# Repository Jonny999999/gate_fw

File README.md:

Custom pcb-design and firmware for an esp32 controlling a self-made automated sliding gate.  
Full Documentation: https://pfusch.zone/automated-sliding-gate

# Changelog V2.0
- Replace old multipurpose board with a custom pcb for controlling the gate
- custom pcb:
  - fully isolate microcontroller from long cables and VFD noise
  - RS485 interface
  - Servo interface to lock the gate
  - Preparation for Encoders
- control motors with VFDs instead of Relays
- firmware rework or rewrite

<br>

## pcb v2.0-isolated-gate-control
- **[KiCad Project](pcb_v2.0-isolated-gate-control/)**
- **[Schematic.pdf](pcb_v2.0-isolated-gate-control/export/schematic.pdf)**
- **[G-code for Isolation Milling](pcb_v2.0-isolated-gate-control/pcb2gcode)**  
  
- **[Connection plan](doc/V2.0_connection-plan.drawio.pdf)**

Schematic + layout preview:  
<p align="center">

</p>

<br>

## Photos
Photos of the V2.0 hardware setup (new custom made pcb, control cabinet and additional box with outsourced power supply and VFDs)

<br>

# Installation
### Install esp-idf
For this project **ESP-IDF v5.5.1** is required  
(with other versions it most likely will not compile)
```bash
#clone the esp-idf repository and check out the required version
git clone -b v5.5.1 --recursive https://github.com/espressif/esp-idf.git ~/esp/v5.5.1/esp-idf
#run installation script in the cloned folder
~/esp/v5.5.1/esp-idf/install.sh esp32
```
### Clone this repo
```
git clone git@github.com:Jonny999999/gate_fw.git
```

# Compilation
### Set up environment
```bash
source ~/esp/v5.5.1/esp-idf/export.sh
```
(run once per terminal)

### Compile
```bash
idf.py build
```

### Upload
**Important:** Since V2.0 the **east Gate has to be slightly open for the upload to work**  
(Since the gpio used for limit switch fully closed has to be pulled low during flashing)
- connect micro-usb cable to ESP32 module on pcb
- press REST and BOOT button
- release RESET button (keep pressing boot)
- run flash command:
```bash
idf.py flash
```
- once "connecting...' successfully, BOOT button can be released  

# Usage

## Quick guide — print this and put it next to the button

### Open button

| What you do | What the gate does |
|---|---|
| **Press briefly** | opens a small gap, enough to walk through |
| **Press briefly again**, right away | makes the gap wider — once for every extra press |
| **Hold** until you hear a long beep | opens fully and stays open |
| **Keep holding** until two short beeps follow | opens fully, then closes again by itself |
| **Press briefly, then press and hold** | opens a small gap, then closes again by itself |

The gate starts moving the moment you press. Just let go when you hear what you want.

### Close button
Press once — the gate closes.

### Remote control
**A** opens fully · **B** closes.

### Stop / cancel
Press **any** button while the gate is moving, or while it is waiting to close by itself.

### When the gate closes by itself
It waits until nobody has crossed the light barrier for a while —
about **10 seconds** after a small gap, about **2 minutes** after opening fully.
Walking through again restarts the wait, so take your time.
The beeps get faster just before it starts moving.
The red lamp flashes briefly once a second for as long as a self-close is waiting.

<br>

---

## Details

### The open button, held down
The gate starts opening the moment you press, and holding on escalates. **Release when you
hear what you want** - each stage announces itself:

| Hold | Meaning | You hear |
|---|---|---|
| release quickly | small gap | one short beep |
| ~0.8 s | open completely | one long tone |
| ~2.5 s | open completely **and close again afterwards** | long tone, then two short ones |

Nothing is committed until you let go, so the familiar "hold it down to open the gate fully"
gesture is unchanged - you simply now have the option of holding on a moment longer.

### Close behind me
Two ways in, depending on how wide you need it:

- **Short press, then press and hold** - opens the small gap, for walking through.
- **Hold the first press ~2.5 s** - opens completely, for driving out.

Either way the gate closes again on its own **once the light barrier has been continuously
free for long enough** - not simply a fixed time after opening.

That distinction is the point: the gate waits until everybody is actually through and
nothing else is coming. Walking in and out, or taking a while with a trailer, restarts the
wait instead of racing a deadline.

| Opening | Barrier must stay clear for |
|---|---|
| small gap (walking through) | 10 s |
| fully open (driving out) | 120 s |

The full opening waits much longer on purpose: you open the gate, walk to the car, start it
and drive out - the barrier may not be interrupted at all for a minute or more, and the gate
must not close in front of you meanwhile.

- An accelerating beep countdown announces the closing over the last 4 seconds, the same one
  the gate uses whenever it starts moving by itself. Interrupting the light barrier during
  the countdown restarts the wait - audibly, because the beeping stops.
- If the light barrier stays interrupted for 20 seconds without a break, the gate gives up
  and stays open (two short beeps, then a long one). Whoever is there is clearly busy.
- Pressing **open** cancels it and leaves the gate open. Pressing **close** closes
  immediately instead of waiting.
- If the barrier is interrupted while it is already closing, it behaves like any other
  close: it pauses, and resumes 4 seconds after the way is clear again.

### Red LED
Two shapes, told apart at a glance:

- **Even blinking** - something went wrong. The faster, the more serious. The LED keeps
  showing the last problem until the next movement is started.
- **Short flash with a gap** - nothing is wrong, but the gate will move on its own in a
  while. Any button press calls it off.

| Pattern | Meaning |
|---|---|
| even, very fast (10/s) | VFD communication failed - the drives could not be reached |
| even, fast (2.5/s) | movement timeout - a limit switch was not reached in time |
| even, slow (1/s) | motor current too high - something was in the way while closing |
| even, very slow (0.5/s) | the light barrier stayed blocked, the movement was given up |
| flash every 0.5 s | movement paused, waiting for the light barrier to clear |
| flash every second | an automatic close is pending |
| steady on (while idle) | the light barrier is interrupted (useful for aligning it) |

The green panel LED is wired in parallel with the buzzer and simply echoes the beeps.

<br>

---

# Legacy -  Old Version V1.0
Left: Photo of control-pcb + RC-module (V1.0)  
Right: Photo of cabinet with power relays and V0.1 board (in V1.0 new board version was used and outsourced due to EMV issues when switching)

# Schema

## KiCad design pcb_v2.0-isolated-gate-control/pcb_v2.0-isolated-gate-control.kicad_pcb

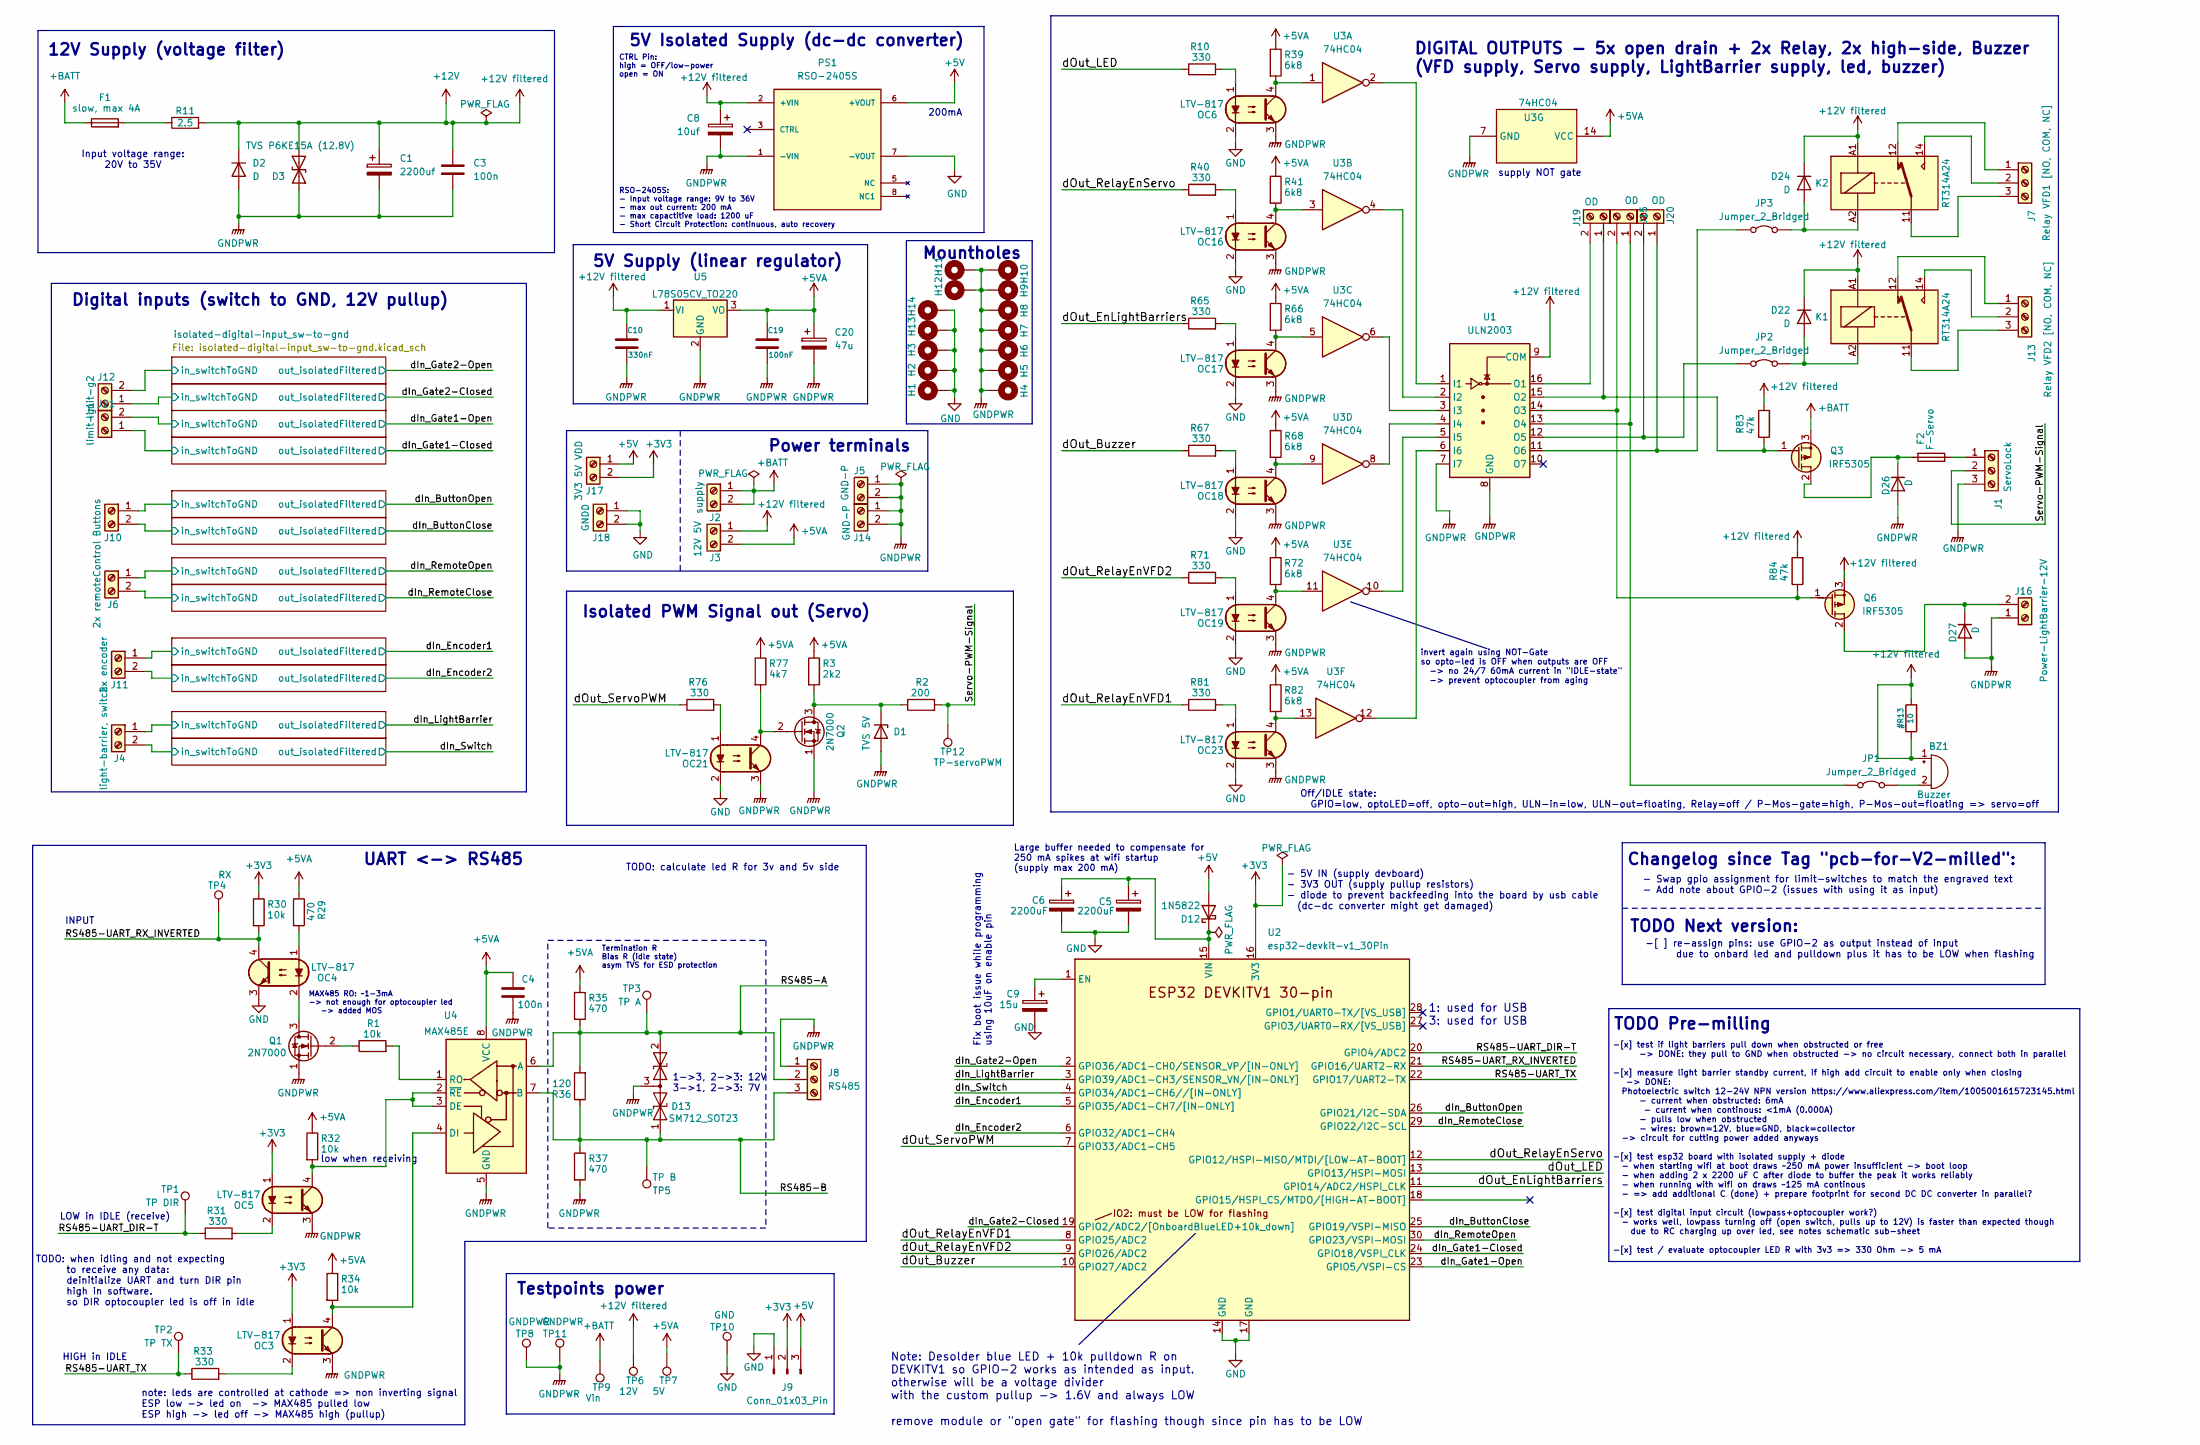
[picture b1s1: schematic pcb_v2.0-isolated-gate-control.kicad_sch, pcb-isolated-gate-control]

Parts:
BZ1: Buzzer; Buzzer_TDK_PS1240P02BT_D12.2mm_H6.5mm
C1: 2200uf; CP_Radial_D10.0mm_P3.80mm
C3, C4: 100n; C_Disc_D7.0mm_W2.5mm_P5.00mm
C5, C6: 2200uF; CP_Radial_D10.0mm_P5.00mm
C8: 10uf; CP_Radial_D5.0mm_P2.50mm
C9: 15u; CP_Radial_D6.3mm_P2.50mm
C10: 330nF; C_Disc_D8.0mm_W5.0mm_P5.00mm
C19: 100nF; C_Disc_D7.0mm_W2.5mm_P5.00mm
C20: 47u; CP_Radial_D5.0mm_P2.50mm
D1: TVS 5V; D_5W_P5.08mm_Vertical_AnodeUp
D2, D22, D24: D; D_T-1_P12.70mm_Horizontal
D3: TVS P6KE15A (12.8V); D_DO-201AE_P15.24mm_Horizontal
D12: 1N5822; D_DO-201AD_P15.24mm_Horizontal
D13: SM712_SOT23; SOT-23
D26, D27: D; D_DO-201_P5.08mm_Vertical_KathodeUp
F1: slow, max 4A; Fuseholder_Automotive-Mini_Fuse11x4x16_Footprint15x5_Inline
F2: F-Servo; Fuseholder_Automotive-Mini_Fuse11x4x16_Footprint15x5_Inline
H1, H2, H3, H4, H5, H6, H7, H8, H9, H10, H11, H12, H13, H14: MountingHole_Pad; MountingHole_2.2mm_NPTH-with-pad_DRC-clearance-error
J1: ServoLock; ScrewTerminal_P5mm_3Pin_FP15x8
J2: supply; ScrewTerminal_P5mm_2Pin_FP10x8
J3: 12V 5V; ScrewTerminal_P5mm_2Pin_FP10x8
J4: light-barrier, switch; ScrewTerminal_P5mm_2Pin_FP10x8
J5, J14: GND-P; ScrewTerminal_P5mm_2Pin_FP10x8
J6: 2x remoteControl; ScrewTerminal_P5mm_2Pin_FP10x8
J7: Relay VFD1 [NO, COM, NC]; ScrewTerminal_P5mm_3Pin_FP15x8
J8: RS485; ScrewTerminal_P5mm_3Pin_FP15x8
J9: Conn_01x03_Pin; PinHeader_1x03_P2.54mm_Vertical
J10: Buttons; ScrewTerminal_P5mm_2Pin_FP10x8
J11: 2x encoder; ScrewTerminal_P5mm_2Pin_FP10x8
J12: limit-g2; ScrewTerminal_P5mm_2Pin_FP10x8
J13: Relay VFD2 [NO, COM, NC]; ScrewTerminal_P5mm_3Pin_FP15x8
J15, J19, J20: OD; ScrewTerminal_P5mm_2Pin_FP10x8
J16: Power-LightBarrier-12V; ScrewTerminal_P5mm_2Pin_FP10x8
J17: 3V3 5V VDD; ScrewTerminal_P5mm_2Pin_FP10x8
J18: GNDD; ScrewTerminal_P5mm_2Pin_FP10x8
J21: limit-g1; ScrewTerminal_P5mm_2Pin_FP10x8
JP1, JP2, JP3: Jumper_2_Bridged; Jumper_P2.54mm_D0.7mm
K1, K2: RT314A24; Relay_SPDT_Schrack-RT1-16A-FormC_RM5mm
OC3, OC4, OC5, OC6, OC16, OC17, OC18, OC19, OC21, OC23: LTV-817; DIP-4_W10.16mm_LongPads
PS1: RSO-2405S; CONV_RSO-2405S; PARTREV 3
Q1, Q2: 2N7000; TO-92_HandSolder
Q3, Q6: IRF5305; TO-220-3_Vertical
R1, R30, R32, R34: 10k; R_Axial_DIN0207_L6.3mm_D2.5mm_P2.54mm_Vertical
R2: 200; R_Axial_DIN0207_L6.3mm_D2.5mm_P2.54mm_Vertical
R3: 2k2; R_Axial_DIN0207_L6.3mm_D2.5mm_P2.54mm_Vertical
R10, R31, R33, R40, R65, R67, R71, R76, R81: 330; R_Axial_DIN0207_L6.3mm_D2.5mm_P2.54mm_Vertical
R11: 2.5; Cement-Power-R_L22_W10_P23_Horizontal
R29, R35, R37: 470; R_Axial_DIN0207_L6.3mm_D2.5mm_P10.16mm_Horizontal
R36: 120; R_Axial_DIN0207_L6.3mm_D2.5mm_P2.54mm_Vertical
R39, R41, R66, R68, R72, R82: 6k8; R_Axial_DIN0207_L6.3mm_D2.5mm_P2.54mm_Vertical
R77: 4k7; R_Axial_DIN0207_L6.3mm_D2.5mm_P10.16mm_Horizontal
R83: 47k; R_Axial_DIN0207_L6.3mm_D2.5mm_P10.16mm_Horizontal
R84: 47k; R_Axial_DIN0207_L6.3mm_D2.5mm_P2.54mm_Vertical
TP1: TP DIR; PinHeader_1x01_P2.54mm_Vertical
TP2: TP TX; PinHeader_1x01_P2.54mm_Vertical
TP3: TP A; PinHeader_1x01_P2.54mm_Vertical
TP4: RX; PinHeader_1x01_P2.54mm_Vertical
TP5: TP B; PinHeader_1x01_P2.54mm_Vertical
TP6: 12V; PinHeader_1x01_P2.54mm_Vertical
TP7: 5V; PinHeader_1x01_P2.54mm_Vertical
TP8, TP11: GNDPWR; PinHeader_1x01_P2.54mm_Vertical
TP9: Vin; PinHeader_1x01_P2.54mm_Vertical
TP10: GND; PinHeader_1x01_P2.54mm_Vertical
TP12: TP-servoPWM; PinHeader_1x01_P2.54mm_Vertical
U1: ULN2003; DIP-16_W7.62mm_LongPads
U2: esp32-devkit-v1_30Pin
U3: 74HC04; DIP-14_W7.62mm_LongPads
U4: MAX485E; DIP-8_W7.62mm_LongPads
U5: L78S05CV_TO220; TO-220-3_Vertical

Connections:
+3V3: J9.2, J17.2, OC3.1, OC5.1, R30.1, U2.16 (3V3); also elsewhere on the board
+5V: D12.2 (A), J9.3, J17.1, PS1.6 (+VOUT)
+5VA: C4.1, C19.1, C20.1, J3.2, R3.1, R29.1, R32.1, R34.1, R35.1, R39.1, R41.1, R66.1, R68.1, R72.1, R77.1, R82.1, TP7.1, U3.14 (VCC), U4.8 (VCC), U5.3 (VO)
+12V: BZ1.1 (+), C1.1, C3.1, C8.1, C10.1, D2.1 (K), D3.1 (A1), D22.1 (K), D24.1 (K), J3.1, K1.A1, K2.A1, PS1.2 (+VIN), Q6.3 (S), R11.2, R83.2, R84.2, TP6.1, U1.9 (COM), U5.1 (VI); also elsewhere on the board
+BATT: F1.1, J2.1, J2.2, Q3.3 (S), TP9.1
/RS485-A: D13.2 (A2), J8.2, R35.2, R36.2, TP3.1, U4.6 (A)
/RS485-B: D13.1 (A1), J8.3, R36.1, R37.1, TP5.1, U4.7 (B)
/RS485-UART_DIR-T: R31.1, TP1.1, U2.20 (GPIO4/ADC2)
/RS485-UART_RX_INVERTED: OC4.4, R30.2, TP4.1, U2.21 (GPIO16/UART2-RX)
/RS485-UART_TX: R33.1, TP2.1, U2.22 (GPIO17/UART2-TX)
/Servo-PWM-Signal: J1.2, R2.2, TP12.1
/dIn_ButtonClose: U2.25 (GPIO19/VSPI-MISO); also elsewhere on the board
/dIn_ButtonOpen: U2.26 (GPIO21/I2C-SDA); also elsewhere on the board
/dIn_Encoder1: U2.5 (GPIO35/ADC1-CH7/[IN-ONLY]); also elsewhere on the board
/dIn_Encoder2: U2.6 (GPIO32/ADC1-CH4); also elsewhere on the board
/dIn_Gate1-Closed: U2.24 (GPIO18/VSPI_CLK); also elsewhere on the board
/dIn_Gate1-Open: U2.23 (GPIO5/VSPI-CS); also elsewhere on the board
/dIn_Gate2-Closed: U2.19 (GPIO2/ADC2); also elsewhere on the board
/dIn_Gate2-Open: U2.2 (GPIO36/ADC1-CH0/SENSOR_VP/[IN-ONLY]); also elsewhere on the board
/dIn_LightBarrier: U2.3 (GPIO39/ADC1-CH3/SENSOR_VN/[IN-ONLY]); also elsewhere on the board
/dIn_RemoteClose: U2.29 (GPIO22/I2C-SCL); also elsewhere on the board
/dIn_RemoteOpen: U2.30 (GPIO23/VSPI-MOSI); also elsewhere on the board
/dIn_Switch: U2.4 (GPIO34/ADC1-CH6//[IN-ONLY]); also elsewhere on the board
/dOut_Buzzer: R67.1, U2.10 (GPIO27/ADC2)
/dOut_EnLightBarriers: R65.1, U2.11 (GPIO14/ADC2/HSPI_CLK)
/dOut_LED: R10.1, U2.13 (GPIO13/HSPI-MOSI)
/dOut_RelayEnServo: R40.1, U2.12 (GPIO12/HSPI-MISO/MTDI/[LOW-AT-BOOT])
/dOut_RelayEnVFD1: R81.1, U2.8 (GPIO25/ADC2)
/dOut_RelayEnVFD2: R71.1, U2.9 (GPIO26/ADC2)
/dOut_ServoPWM: R76.1, U2.7 (GPIO33/ADC1-CH5)
/isolated-digital-input_sw-to-gnd1/in_switchToGND: J12.1; also elsewhere on the board
/isolated-digital-input_sw-to-gnd2/in_switchToGND: J21.2; also elsewhere on the board
/isolated-digital-input_sw-to-gnd3/in_switchToGND: J21.1; also elsewhere on the board
/isolated-digital-input_sw-to-gnd4/in_switchToGND: J10.1; also elsewhere on the board
/isolated-digital-input_sw-to-gnd5/in_switchToGND: J10.2; also elsewhere on the board
/isolated-digital-input_sw-to-gnd6/in_switchToGND: J11.1; also elsewhere on the board
/isolated-digital-input_sw-to-gnd7/in_switchToGND: J11.2; also elsewhere on the board
/isolated-digital-input_sw-to-gnd8/in_switchToGND: J6.1; also elsewhere on the board
/isolated-digital-input_sw-to-gnd9/in_switchToGND: J6.2; also elsewhere on the board
/isolated-digital-input_sw-to-gnd10/in_switchToGND: J4.1; also elsewhere on the board
/isolated-digital-input_sw-to-gnd/in_switchToGND: J12.2; also elsewhere on the board
GND: C5.2, C6.2, C9.2, H1.1, H2.1, H3.1, H13.1, H14.1, J9.1, J18.1, J18.2, OC4.3, OC6.2, OC16.2, OC17.2, OC18.2, OC19.2, OC21.2, OC23.2, PS1.7 (-VOUT), TP10.1, U2.14 (GND), U2.17 (GND); also elsewhere on the board
unnamed: BZ1.2 (-), JP1.2 (B)
unnamed: D1.1 (K), Q2.3 (D), R2.1, R3.2
unnamed: C5.1, C6.1, D12.1 (K), U2.15 (VIN)
unnamed: D22.2 (A), JP2.2 (B), K1.A2
unnamed: D24.2 (A), JP3.2 (B), K2.A2
unnamed: D26.1 (K), F2.2, Q3.2 (D)
unnamed: D27.1 (K), J16.2, Q6.2 (D)
unnamed: F1.2, R11.1
unnamed: F2.1, J1.1
unnamed: J7.1, K2.12
unnamed: J7.2, K2.14
unnamed: J7.3, K2.11
unnamed: J13.1, K1.12
unnamed: J13.2, K1.14
unnamed: J13.3, K1.11
unnamed: J15.1, JP1.1 (A), U1.13 (O4)
unnamed: J15.2, Q6.1 (G), R84.1, U1.14 (O3)
unnamed: J19.1, Q3.1 (G), R83.1, U1.15 (O2)
unnamed: J19.2, U1.16 (O1)
unnamed: J20.1, JP3.1 (A), U1.11 (O6)
unnamed: J20.2, JP2.1 (A), U1.12 (O5)
unnamed: OC3.2, R33.2
unnamed: OC4.1, R29.2
unnamed: OC5.2, R31.2
unnamed: OC6.1, R10.2
unnamed: OC6.4, R39.2, U3.1
unnamed: OC16.1, R40.2
unnamed: OC16.4, R41.2, U3.3
unnamed: OC17.1, R65.2
unnamed: OC17.4, R66.2, U3.5
unnamed: OC18.1, R67.2
unnamed: OC18.4, R68.2, U3.9
unnamed: OC19.1, R71.2
unnamed: OC19.4, R72.2, U3.11
unnamed: OC21.1, R76.2
unnamed: OC23.1, R81.2
unnamed: OC23.4, R82.2, U3.13
unnamed: OC4.2, Q1.3 (D)
unnamed: Q1.2 (G), R1.1
unnamed: OC21.4, Q2.2 (G), R77.2
unnamed: U1.1 (I1), U3.2
unnamed: U1.2 (I2), U3.4
unnamed: U1.3 (I3), U3.6
unnamed: U1.4 (I4), U3.8
unnamed: U1.5 (I5), U3.10
unnamed: U1.6 (I6), U3.12
unnamed: C9.1, U2.1 (EN)
unnamed: OC5.4, R32.2, U4.2 (~RE), U4.3 (DE)
unnamed: OC3.4, R34.2, U4.4 (DI)
unnamed: R1.2, U4.1 (RO)

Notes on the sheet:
INPUT
note: leds are controlled at cathode => non inverting signal ESP low -> led on -> MAX485 pulled low ESP high -> led off -> MAX485 high (pullup)
invert again using NOT-Gate so opto-led is OFF when outputs are OFF -> no 24/7 60mA current in "IDLE-state" -> prevent optocoupler from aging
- Swap gpio assignment for limit-switches to match the engraved text - Add note about GPIO-2 (issues with using it as input)
Isolated PWM Signal out (Servo)
LOW in IDLE (receive)
-[x] test if light barriers pull down when obstructed or free -> DONE: they pull to GND when obstructed -> no circuit necessary, connect both in parallel -[x] measure light barrier standby current, if high add circuit to enable only when closing -> DONE: Photoelectric switch 12-24V NPN version http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
Off/IDLE state: GPIO=low, optoLED=off, opto-out=high, ULN-in=low, ULN-out=floating, Relay=off / P-Mos-gate=high, P-Mos-out=floating => servo=off
5V Supply (linear regulator)
Testpoints power
12V Supply (voltage filter)
Large buffer needed to compensate for 250 mA spikes at wifi startup (supply max 200 mA)
1: used for USB 3: used for USB
5V Isolated Supply (dc-dc converter)
UART <-> RS485
TODO Next version:
MAX485 RO: ~1-3mA -> not enough for optocoupler led -> added MOS
1->3, 2->3: 12V 3->1, 2->3: 7V
supply NOT gate
TODO: when idling and not expecting to receive any data: deinitialize UART and turn DIR pin high in software. so DIR optocoupler led is off in idle
DIGITAL OUTPUTS - 5x open drain + 2x Relay, 2x high-side, Buzzer (VFD supply, Servo supply, LightBarrier supply, led, buzzer)
Power terminals
-[ ] re-assign pins: use GPIO-2 as output instead of input due to onbard led and pulldown plus it has to be LOW when flashing
- 5V IN (supply devboard) - 3V3 OUT (supply pullup resistors) - diode to prevent backfeeding into the board by usb cable (dc-dc converter might get damaged)
Input voltage range: 20V to 35V
Mountholes
Digital inputs (switch to GND, 12V pullup)
Changelog since Tag "pcb-for-V2-milled":
CTRL Pin: high = OFF/low-power open = ON
Fix boot issue while programming using 10uF on enable pin
200mA
Termination R Bias R (idle state) asym TVS for ESD protection
low when receiving
TODO Pre-milling
Note: Desolder blue LED + 10k pulldown R on DEVKITV1 so GPIO-2 works as intended as input. otherwise will be a voltage divider with the custom pullup -> 1.6V and always LOW remove module or "open gate" for flashing though since pin has to be LOW
HIGH in IDLE
RSO-2405S: - Input voltage range: 9V to 36V - max out current: 200 mA - max capactitive load: 1200 uF - Short Circuit Protection: continuous, auto recovery
TODO: calculate led R for 3v and 5v side

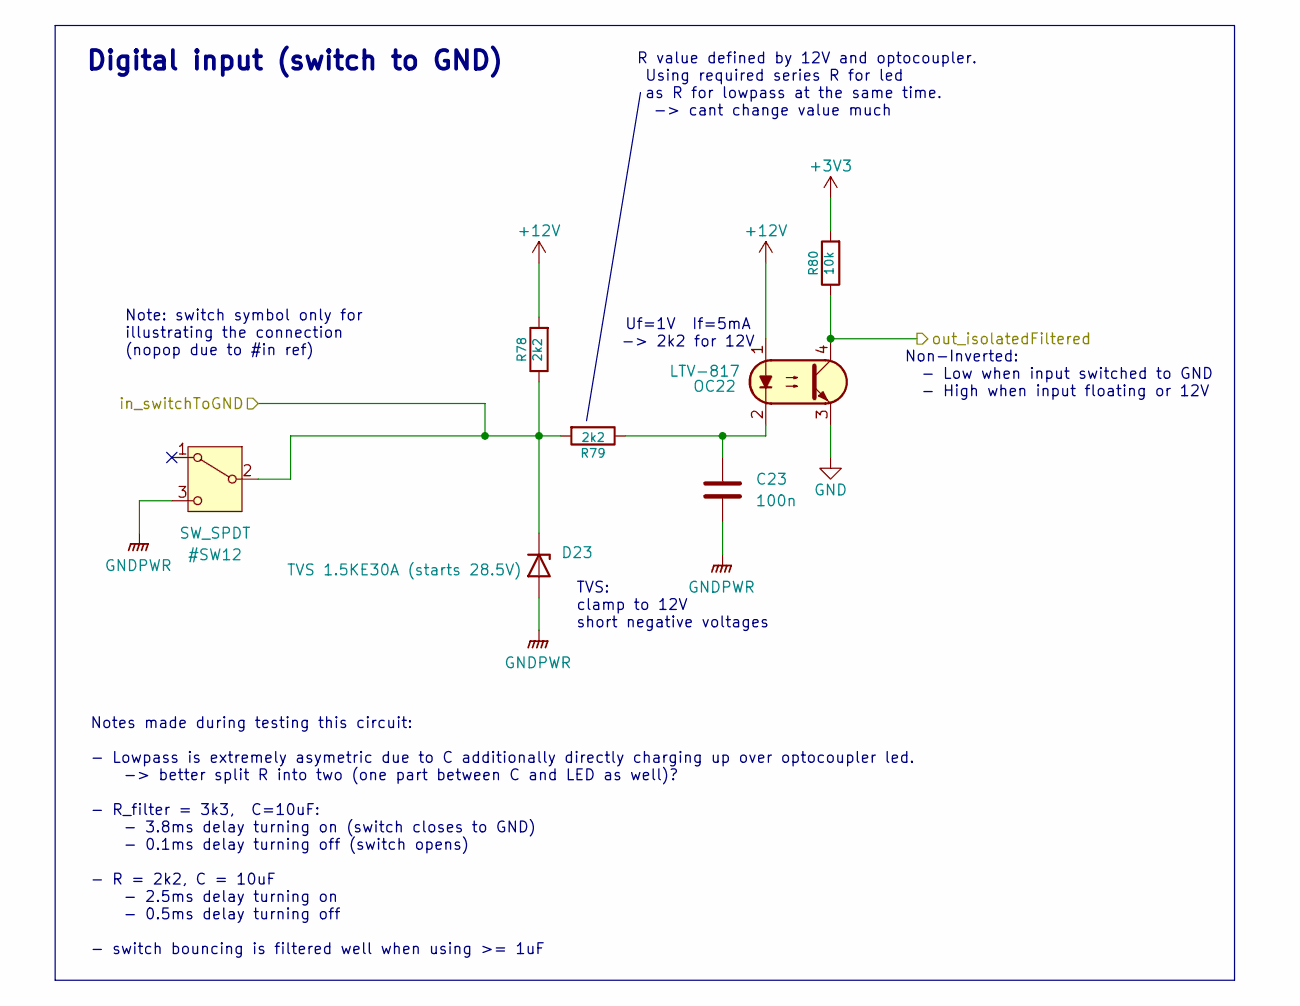
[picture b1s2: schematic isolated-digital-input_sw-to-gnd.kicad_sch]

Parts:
C23: 100n; C_DualType__Disc-7.0x2.5mm-P5mm__Elko-D5mm-P2.5mm
D23: TVS 1.5KE30A (starts 28.5V); D_DO-41_SOD81_P12.70mm_Horizontal
OC22: LTV-817; DIP-4_W10.16mm_LongPads
R78, R79: 2k2; R_Axial_DIN0207_L6.3mm_D2.5mm_P10.16mm_Horizontal
R80: 10k; R_Axial_DIN0207_L6.3mm_D2.5mm_P2.54mm_Vertical

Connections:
+3V3: R80.2; also elsewhere on the board
+12V: OC22.1, R78.2; also elsewhere on the board
/dIn_Switch: OC22.4, R80.1; also elsewhere on the board
GND: OC22.3; also elsewhere on the board
unnamed: C23.1, OC22.2, R79.1

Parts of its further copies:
C2, C11, C12, C13, C14, C15, C16, C17, C18, C21, C22: 100n; C_DualType__Disc-7.0x2.5mm-P5mm__Elko-D5mm-P2.5mm
OC1, OC2, OC7, OC8, OC9, OC10, OC11, OC12, OC13, OC14, OC20: LTV-817; DIP-4_W10.16mm_LongPads
R12, R25, R26, R28, R38, R43, R44, R46, R47, R49, R50, R52, R53, R55, R56, R58, R59, R61, R62, R69, R73, R74: 2k2; R_Axial_DIN0207_L6.3mm_D2.5mm_P10.16mm_Horizontal
R27, R42, R45, R48, R51, R54, R57, R60, R63, R70, R75: 10k; R_Axial_DIN0207_L6.3mm_D2.5mm_P2.54mm_Vertical

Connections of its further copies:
+3V3: R27.2, R42.2, R45.2, R48.2, R51.2, R54.2, R57.2, R60.2, R63.2, R70.2, R75.2; also elsewhere on the board
+12V: OC1.1, OC2.1, OC7.1, OC8.1, OC9.1, OC10.1, OC11.1, OC12.1, OC13.1, OC14.1, OC20.1, R12.2, R25.2, R28.2, R43.2, R46.2, R49.2, R52.2, R55.2, R58.2, R61.2, R73.2; also elsewhere on the board
/dIn_ButtonClose: OC12.4, R57.1; also elsewhere on the board
/dIn_ButtonOpen: OC11.4, R54.1; also elsewhere on the board
/dIn_Encoder1: OC13.4, R60.1; also elsewhere on the board
/dIn_Encoder2: OC14.4, R63.1; also elsewhere on the board
/dIn_Gate1-Closed: OC10.4, R51.1; also elsewhere on the board
/dIn_Gate1-Open: OC9.4, R48.1; also elsewhere on the board
/dIn_Gate2-Closed: OC8.4, R45.1; also elsewhere on the board
/dIn_Gate2-Open: OC7.4, R42.1; also elsewhere on the board
/dIn_LightBarrier: OC20.4, R75.1; also elsewhere on the board
/dIn_RemoteClose: OC2.4, R70.1; also elsewhere on the board
/dIn_RemoteOpen: OC1.4, R27.1; also elsewhere on the board
/isolated-digital-input_sw-to-gnd1/in_switchToGND: R43.1, R44.2; also elsewhere on the board
/isolated-digital-input_sw-to-gnd2/in_switchToGND: R46.1, R47.2; also elsewhere on the board
/isolated-digital-input_sw-to-gnd3/in_switchToGND: R49.1, R50.2; also elsewhere on the board
/isolated-digital-input_sw-to-gnd4/in_switchToGND: R52.1, R53.2; also elsewhere on the board
/isolated-digital-input_sw-to-gnd5/in_switchToGND: R55.1, R56.2; also elsewhere on the board
/isolated-digital-input_sw-to-gnd6/in_switchToGND: R58.1, R59.2; also elsewhere on the board
/isolated-digital-input_sw-to-gnd7/in_switchToGND: R61.1, R62.2; also elsewhere on the board
/isolated-digital-input_sw-to-gnd8/in_switchToGND: R25.1, R26.2; also elsewhere on the board
/isolated-digital-input_sw-to-gnd9/in_switchToGND: R28.1, R69.2; also elsewhere on the board
/isolated-digital-input_sw-to-gnd10/in_switchToGND: R73.1, R74.2; also elsewhere on the board
/isolated-digital-input_sw-to-gnd/in_switchToGND: R12.1, R38.2; also elsewhere on the board
GND: OC1.3, OC2.3, OC7.3, OC8.3, OC9.3, OC10.3, OC11.3, OC12.3, OC13.3, OC14.3, OC20.3; also elsewhere on the board
unnamed: C2.1, OC1.2, R26.1
unnamed: C11.1, OC7.2, R38.1
unnamed: C12.1, OC8.2, R44.1
unnamed: C13.1, OC9.2, R47.1
unnamed: C14.1, OC10.2, R50.1
unnamed: C15.1, OC11.2, R53.1
unnamed: C16.1, OC12.2, R56.1
unnamed: C17.1, OC13.2, R59.1
unnamed: C18.1, OC14.2, R62.1
unnamed: C21.1, OC2.2, R69.1
unnamed: C22.1, OC20.2, R74.1

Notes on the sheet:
Note: switch symbol only for illustrating the connection (nopop due to #in ref)
R value defined by 12V and optocoupler. Using required series R for led as R for lowpass at the same time. -> cant change value much
TVS: clamp to 12V short negative voltages
Digital input (switch to GND)
Non-Inverted: - Low when input switched to GND - High when input floating or 12V
Notes made during testing this circuit: - Lowpass is extremely asymetric due to C additionally directly charging up over optocoupler led. -> better split R into two (one part between C and LED as well)? - R_filter = 3k3, C=10uF: - 3.8ms delay turning on (switch closes to GND) - 0.1ms delay turning 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
Uf=1V If=5mA -> 2k2 for 12V

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
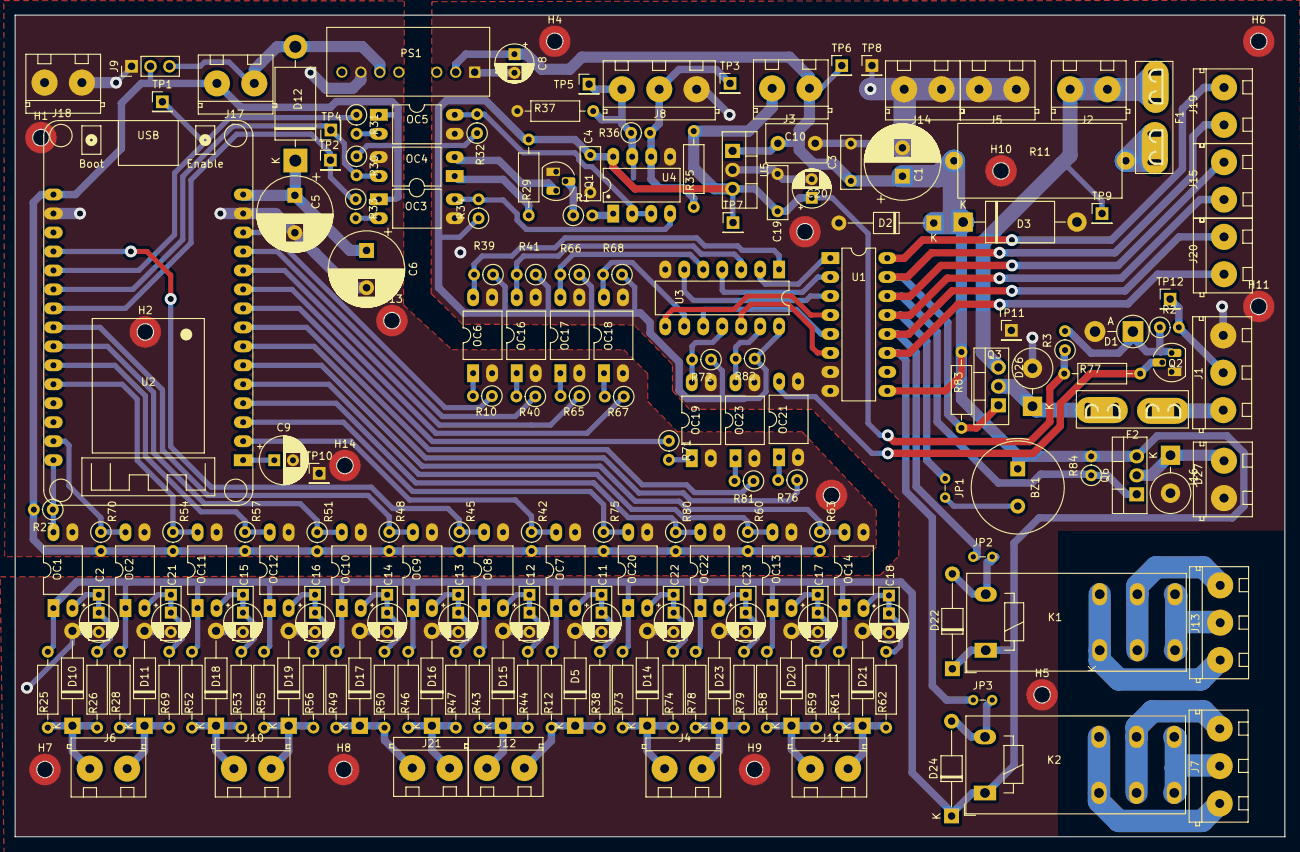
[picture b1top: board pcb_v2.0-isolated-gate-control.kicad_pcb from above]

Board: 4 copper layers, 170.0 x 110.0 mm, 195 parts (1 on the bottom side), 106 nets.

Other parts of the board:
D5, D10, D11, D14, D15, D16, D17, D18, D19, D20, D21: TVS P6KE15A (12.8V); D_DO-41_SOD81_P12.70mm_Horizontal

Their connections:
/isolated-digital-input_sw-to-gnd1/in_switchToGND: D15.1 (K); also elsewhere on the board
/isolated-digital-input_sw-to-gnd2/in_switchToGND: D16.1 (K); also elsewhere on the board
/isolated-digital-input_sw-to-gnd3/in_switchToGND: D17.1 (K); also elsewhere on the board
/isolated-digital-input_sw-to-gnd4/in_switchToGND: D18.1 (K); also elsewhere on the board
/isolated-digital-input_sw-to-gnd5/in_switchToGND: D19.1 (K); also elsewhere on the board
/isolated-digital-input_sw-to-gnd6/in_switchToGND: D20.1 (K); also elsewhere on the board
/isolated-digital-input_sw-to-gnd7/in_switchToGND: D21.1 (K); also elsewhere on the board
/isolated-digital-input_sw-to-gnd8/in_switchToGND: D10.1 (K); also elsewhere on the board
/isolated-digital-input_sw-to-gnd9/in_switchToGND: D11.1 (K); also elsewhere on the board
/isolated-digital-input_sw-to-gnd10/in_switchToGND: D14.1 (K); also elsewhere on the board
/isolated-digital-input_sw-to-gnd/in_switchToGND: D5.1 (K); also elsewhere on the board

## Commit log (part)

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2022-05-27 init (esp-idf sample_project)
    copy sample project from esp-idf
2022-05-27 CPP support: Rename main.c to main.cpp
2022-05-27 Modifications for cpp compatibility
    - extern C around libraries and main function
    - Include common libraries
    - Create basic 'gate' class (no functionality)
2022-05-27 README: Remove sample, Add pin assignment
2022-05-27 README: Add install/compile instructions
2022-05-27 Create config.hpp, Add all gpio pins
    Create separate file for configuration
    Add all currently used gpio pins to this file
    Modify main.cpp to use those variables
2022-05-27 Add function 'statusReport'
    Add function statusReport in main.cpp
    Currently is run every 5s and displays the current state of the buttons
    and switches
2022-05-28 Create component gpio_evaluateSwitch
    - Copy library written for avr projects
    - Modify files to work with esp32 instead of avr
    - create component for esp-idf (CMakeLists.txt)
    Note this broke the `make` command when including this library " fatal
    error: gpio_evaluateSwitch.hpp: No such file or directory"
    However `idf.py` works fine
2022-05-28 Use evaluatedSwitch class for Open/Close buttons
    - create objects for the two switches in config.hpp (so they are
    globally available)
    - main.cpp: add call off handle functions in the main loop
    - main.cpp: change status report function to use evaluated object for
    start/stop buttons instead of reading gpio
    - main.cpp: add log output to print button events for testing the new
2022-05-28 Add functional 'gate class'
    - add class with variables and functions according to the created
    diagram to main.cpp
    - rename instances from gate_right to gateRight
    - add status of gate to status report
2022-05-28 Outsource gate class (gate.cpp/hpp, config.cpp)
    - move gate class and declaration from main.cpp to gate.hpp
    - move gate class definition from main.cpp to gate.cpp
    - create constructor for gate object with configuration instead of
    accessing the variables directly
    - move declaration of all objects to config.hpp
    - move all config definitions to config.cpp (instead of all in hpp) this
2022-05-28 Create control.hpp - control gate with buttons
    - Create function 'control' in separate file control.hpp
    - Add control state and information to status report in main.cpp
    - increase status report interval
    - add gate.setDuration function to gate.cpp (was not defined)
2022-05-29 Add logging output, swap buttons, add name
    - add logging output to all functions with different loglevels
    - add name string to gate class
    - add name to object initialization in config
    - swap gpio pin of buttons
2022-05-29 Fix random outputs bug (direction definition)
    All outputs were defined as inputs (direction definition had no effect)
    thus the mosfets switched randomly (floating)
    - fix direction definition (must select pad each time before set direction)
    - comment out gate and control files (not wanted in i/o test)
2022-05-29 Fix multiple gate switches when long pressed
    when pressing both buttons the gate selection switched multiple times
    (only the delay for beeping limited the interval)
    - fixed locking so buttons have to be released first before next switch
    is possible
    Tested: I/O test works as described in first commit! the 2 gates can be
    individually operated by pressing open/close buttons. Switch between
2022-05-29 Fix random outputs bug (direction definition)
    All outputs were defined as inputs (direction definition had no effect)
    thus the mosfets switched randomly (floating)
    - add pad select function before each set_direction function in gate.cpp
    and gpio_evaluateSwitch.cpp
    - add beep at start of main functon
    - add log output in evaluateswitch.cpp
2022-05-29 Add and optimize comments
    added more and optimized comments in almost all files to make the code more
    readable and structured
2022-05-29 Fix 'open completely', Adjust durations
    - fix bug where 'open completely' was hard to achieve (button had to be
    pressed at the exact right time). Now the open button has to be
    pressed continuously for more than 800ms to trigger 'open completely'
    event
    - decreased duration of 'open slightly' to 1.2s according to old project
    - adjust lastaction timeout
2022-05-30 Create buzzer_t class (buzzer.hpp/cpp)
    Crate class for controlling the buzzer with the following features:
    - is run in another task
    - queues up beep commands (if another beep command is run while a
    previous one is still processing)
    Steps in this commit:
    - create files buzzer.cpp and .hpp with the new class
2022-05-30 Add beeping, Change gate::stop(): add stopReason
    - use buzzer object in gate.cpp and control.hpp for signaling certain
    events
    - add stopReason enum to gate::stop function. This reduces duplicate
    code for logging and beeping
2022-05-30 Add inputs of remote control (testing)
    - Add 2 inputs of remote control as evaluatedSwitch objects
    - Add test output in main.cpp to test whether the signal is detected,
    since receiver is connected to adc input
2022-05-30 Add functionality to remote control inputs
    - Invert switches (noticed while testing that relays switch to gnd,
    pulldown soldered on pcb)
    - Add code for the new inputs from remote control to control.hpp
    - open gate when remoteOpen rising edge
    - close gate when remoteClose rising edge
    - stop gates when any remote input (or any button pressed)
2022-05-30 Fix 'open slightly' duration, Decrease beeps
    - fix open slightly duration (was increased even when only pressed once,
    since countPressed started at 1)
    - make beeps even shorter
2022-05-30 README: required version, upload/usage instructions
    - Add note that ESP-IDF version v4.4.1 is required
    - Add detailed instructions for how to connect and flash the controller
    - Add usage description (how to use the gate)
2022-08-27 Add 'WAITING' state - wait for standstill
    When starting the gate while it is moving (e.g. immediately restart after stop) the motors may start
    rotating in the wrong direction.
    This results in a fatal crash - gate moves to other than intended limit
    switch and will not stop before timeout.
    -> Add delay between stop and IDLE, thus preventing an immediate re-start
    [untested]
2022-08-27 Add handling of case 'wrong motor direction'
    In addition to prevent start in wrong direction in the first place (see
    last commit), add handling of case when ending up at wrong limit switch
    again.
    see updated function diagram
    quite large change to statemachine:
    - rename states
2022-08-28 Optimize logging; Remove duplicate code 'stop-condition'
    - Optimize logging:
    - make use of different loglevels
    - change log formatting to one standard
    - use separate function for state changes and logging - removes duplicate code
    gate.cpp:
    - outsource stop condition used in 4 cases of gate statemachine in a
2022-08-29 Remove unnecessary log output
2022-08-29 Update README; Rename function diagram
    minor changes to readme
    - fix newlines
    - remove no longer supported make command
2024-10-27 Add VFD datasheets + modbus test (from cable-length-cutter repo)
2024-12-23 Add connection-plan, Add photos to README
2024-12-23 Add assets: gear 3d-models, labels, schema, overview.pdf
2024-12-23 Change project structure (separate old fw to fw_v1.0-legacy)
2024-12-23 Add RS485 test: Turn on vfd + set freq via modbus - works
    Note: hardware setup: MAX485 supplied with 5V
    with custom mosfet level shifters
    -> DIR and TX pins are inverted in software
2024-12-23 Add support for reading registers (reading voltage, current, temperature)
2024-12-24 Fix unnecessary delay when receiving
2024-12-24 Create kicad project pcb_v2.0-isolated-gate-control - Add esp32, RS485, digital-in, supply
2024-12-24 pcb: outsrc isolated-dig-in, assign pins, Add supply, 12V out, servo-pwm
2024-12-25 pcb: Add Relays, mosfet-out, terminals, Fix RS485 isolation
2024-12-25 pcb: change footprints + arrange groups individually for saving space
2024-12-25 pcb: arrange almost all groups inside 100x165 pcb
2024-12-26 pcb: Re-assign FP, Optimize arrangement, Proof-of-concept routing
2024-12-27 pcb: remap gpio-pins, finish proof-of-concept routing (to evaluate arrangement)
2024-12-28 pcb: routing complete (DRC pass)
2024-12-28 pcb: Add text, testpoints, mounting-holes
2024-12-29 pcb: Add NOT-Gate (optocouplers off in idle), Replace ULN28 with 7Ch
2024-12-31 pcb: Cleanup Schematic, arrange, replace legacy-symbols, optimize for ERC pass
2024-12-31 Add pcb2gcode configs + script (copied from other project)
2025-01-01 pcb: finish todos, Fix esp32 power issues, document tests, dualType C footprint
2025-01-01 Extend pcb2gcode script: add pass (mill away copper), Add gcode - [MILLED PCB]
2025-01-02 pcb: Arrange silk/fab text, Mark front-solder, Add schematic+layout export
2025-01-02 Add note about planned V2.0 to README
2025-01-05 pcb: fix minor layout issues (missing text, spacing)
2025-01-05 fw: Fix pin-assignment, Invert IO passthrough level
2025-01-06 fw: Fix invalid UART signal inversion, Re-assign pins
2025-01-06 fw: outsource and reorder io-test, increment VFD freq
2025-01-06 pcb: Add Changelog, Note about GPIO-2 input issue
2025-01-26 Add class VFD, main: switch to c++, modbus: use esp-error-codes
    Add class VFD for abstracting the RS485 communication
    Test two class instances in main loop, test with one vfd success
2025-01-26 Create class Gate for controlling one gate (WIP)
2025-02-08 Rework gate class (compiles, basic logging test success)
2025-02-09 Add option to invert limit-switches, Optimize logging, variable-names, structure
2025-02-19 Add control.cpp for controlling 2 gates with buttons [WIP]
    note: no new features, rewrite of V1
    WIP: does not compile yet
2025-02-20 Gate: make "wait-for-vfd-startup" non-blocking, Add open/closeCompletely methods
2025-02-20 Add evaluatedSwitch class, Optimize control task (functional)
2025-02-20 Enable modbus loglevel
2025-02-21 Change baudrate, loglevel, default vfd freq (for first hw test)
2025-02-22 Increase delay, logging, baudrate 9600 - gate not closing, stop error G2
2025-02-22 Run VFD test only (VFD1 reverse) - VFD ACK but not starting
2025-02-22 Doc: Add VFD parameters, connection-plan, Update terminal-labels
2025-02-22 Modbus: Add multiple retries in send_modbus_command
2025-02-22 Fix VFD Reverse not working (wrong REG value in manual)
2025-02-22 Add logging of VFD current when closing
2025-02-24 Change addresses for VFDs 1 / 2 to 11 / 77, Minor Optimizations (beep, button)
2025-02-25 Add vfd current monitoring (stop closing when threshold exceeded), beep at limit change
2025-02-26 Adjust parameters: freq 50Hz, switch-press-time, move-durations, timeout, loglevel
2025-02-26 Gate: Fix inf. start loop on VFD com fail, Add support for Fault-LED
2025-02-26 Add photos of V2.0, Update Readme
2025-03-24 Add light-barrier gpio-pin to controlConfig (pass to task)
2025-03-27 [WIP] Add 'pause / resume' functionality to gate class (WIP, not compiling)
2025-03-30 Increase VFD turn-off-timeout (1h -> 2.5h), Fix button bounce - Increase button deadtime (20->40ms)
2025-04-03 Revert vfd-startup-delay, Increase turn-off-timeout to 3h
2025-04-13 Add light-barrier support to control, Gate pause-timeout (compiles, untested)
2025-04-13 Add fault-led blinking in MOVEMENT_PAUSED (waiting for barrier)
2025-04-17 Adjust thresholds, Fix led-blinking and beeping (works as intended)
2025-04-18 Update connection+wiring plan (redraw switches, flash note)
2025-04-19 Add debug beep / led-passthrough for barrier, Add Beep at close start
2025-04-20 Fix remote-control close button ignoring barrier check
